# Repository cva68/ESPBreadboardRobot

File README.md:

# ESP32 Breadboard Robot
A device designed to mount to a breadboard to breakout the ESP32-C3 devboard pins, add an LED matrix, dual motor drivers, photoresistor inputs for line following, and two buttons.
Designed to mimic (some) functionality of the BBC micro:bit + Kitronic Motor Driver Board combo currently used by Lincoln High School for teaching electronics, at a lower cost and in a more convenient package.

## Software
The software is designed to support exporting blocks from MakeCode directly into main.py. Basic, LED, Input and Motor blocks are currently supported. src/ and lib/ have the required files to enable this.

## Hardware
The schematic and PCB designs are included in /hardware.

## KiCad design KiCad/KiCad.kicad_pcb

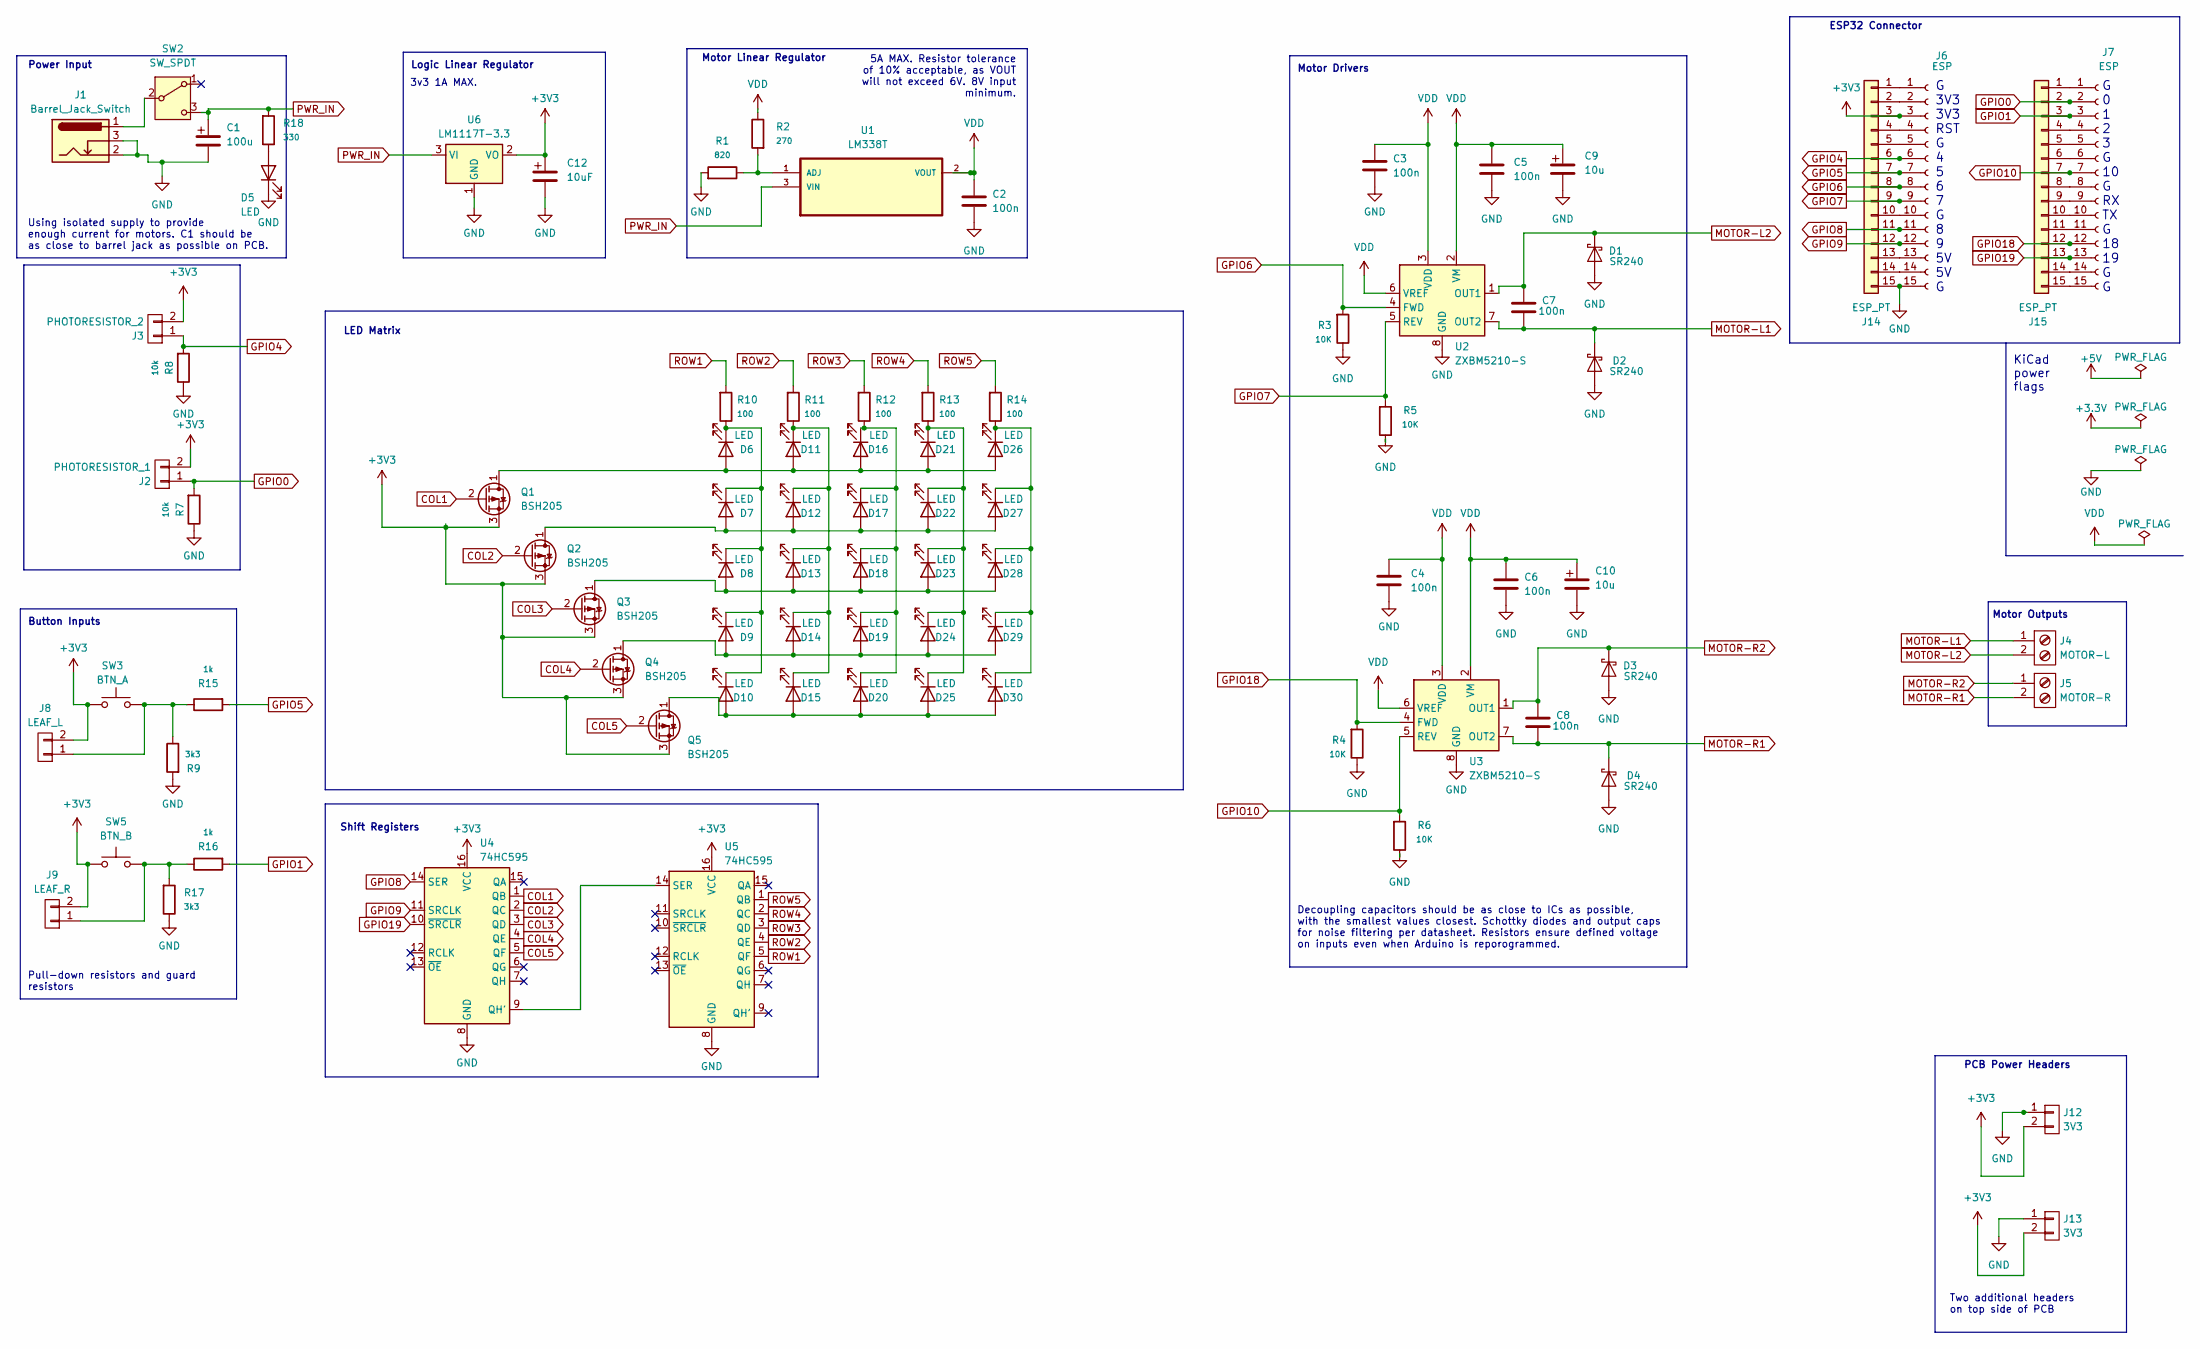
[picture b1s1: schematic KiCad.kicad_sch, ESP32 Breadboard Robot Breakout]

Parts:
C1: 100u; CP_Radial_D8.0mm_P3.50mm
C2, C3, C4, C5, C6, C7, C8: 100n; C_Rect_L4.6mm_W3.0mm_P2.50mm_MKS02_FKP02
C9, C10: 10u; CP_Radial_D8.0mm_P3.50mm
C12: 10uF; CP_Radial_D5.0mm_P2.00mm
D1, D2, D3, D4: SR240; D_DO-35_SOD27_P2.54mm_Vertical_AnodeUp
D5: LED; LED_D5.0mm
D6, D7, D8, D9, D10, D11, D12, D13, D14, D15, D16, D17, D18, D19, D20, D21, D22, D23, D24, D25, D26, D27, D28, D29, D30: LED; LED_1206_3216Metric_Pad1.42x1.75mm_HandSolder
J1: Barrel_Jack_Switch; BarrelJack_Horizontal
J2: PHOTORESISTOR_1; PinHeader_1x02_P2.54mm_Vertical
J3: PHOTORESISTOR_2; PinHeader_1x02_P2.54mm_Vertical
J4: MOTOR-L; TerminalBlock_Phoenix_MKDS-1,5-2-5.08_1x02_P5.08mm_Horizont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
J5: MOTOR-R; TerminalBlock_Phoenix_MKDS-1,5-2-5.08_1x02_P5.08mm_Horizont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
J6, J7: ESP; PinHeader_1x15_P2.54mm_Vertical
J8: LEAF_L; PinHeader_1x02_P2.54mm_Vertical
J9: LEAF_R; PinHeader_1x02_P2.54mm_Vertical
J12, J13: 3V3; PinHeader_1x02_P2.54mm_Vertical
J14, J15: ESP_PT; PinHeader_1x15_P2.54mm_Vertical
Q1, Q2, Q3, Q4, Q5: BSH205; SOT-23-3
R1: 820; R_Axial_DIN0207_L6.3mm_D2.5mm_P2.54mm_Vertical
R2: 270; R_Axial_DIN0207_L6.3mm_D2.5mm_P2.54mm_Vertical
R3, R4, R5, R6: 10K; R_Axial_DIN0207_L6.3mm_D2.5mm_P2.54mm_Vertical
R7, R8: 10k; R_Axial_DIN0207_L6.3mm_D2.5mm_P2.54mm_Vertical
R9, R17: 3k3; R_Axial_DIN0207_L6.3mm_D2.5mm_P2.54mm_Vertical
R10, R11, R12, R13, R14: 100; R_Axial_DIN0207_L6.3mm_D2.5mm_P2.54mm_Vertical
R15, R16: 1k; R_Axial_DIN0207_L6.3mm_D2.5mm_P2.54mm_Vertical
R18: 330; R_Axial_DIN0207_L6.3mm_D2.5mm_P2.54mm_Vertical
SW2: SW_SPDT; SW_Slide-03_Wuerth-WS-SLTV_10x2.5x6.4_P2.54mm
SW3: BTN_A; SW_PUSH_6mm_H5mm
SW5: BTN_B; SW_PUSH_6mm_H5mm
U1: LM338T; TO-220-3_Horizontal_TabDown
U2, U3: ZXBM5210-S; SOIC-8_3.9x4.9mm_P1.27mm
U4, U5: 74HC595; SOIC-16_4.55x10.3mm_P1.27mm
U6: LM1117T-3.3; TO-220-3_Horizontal_TabDown

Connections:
+3V3: C12.1, J2.2, J3.2, J6.3, J8.2, J9.2, J12.2, J13.2, J14.3, Q1.3 (S), Q2.3 (S), Q3.3 (S), Q4.3 (S), Q5.3 (S), SW3.1, SW5.1, U4.16 (VCC), U5.16 (VCC), U6.2 (VO)
COL1: Q1.2 (G), U4.1 (QB)
COL2: Q2.2 (G), U4.2 (QC)
COL3: Q3.2 (G), U4.3 (QD)
COL4: Q4.2 (G), U4.4 (QE)
COL5: Q5.2 (G), U4.5 (QF)
GND: C1.2, C2.2, C3.2, C4.2, C5.2, C6.2, C9.2, C10.2, C12.2, D1.2 (A), D2.2 (A), D3.2 (A), D4.2 (A), D5.1 (K), J1.2, J1.3, J6.15, J12.1, J13.1, J14.15, R1.1, R3.2, R4.2, R5.2, R6.2, R7.2, R8.2, R9.1, R17.2, U2.8 (GND), U3.8 (GND), U4.8 (GND), U5.8 (GND), U6.1 (GND)
GPIO0: J2.1, J7.2, J15.2, R7.1
GPIO1: J7.3, J15.3, R16.1
GPIO4: J3.1, J6.6, J14.6, R8.1
GPIO5: J6.7, J14.7, R15.1
GPIO6: J6.8, J14.8, R3.1, U2.4 (FWD)
GPIO7: J6.9, J14.9, R5.1, U2.5 (REV)
GPIO8: J6.11, J14.11, U4.14 (SER)
GPIO9: J6.12, J14.12, U4.11 (SRCLK)
GPIO10: J7.7, J15.7, R6.1, U3.5 (REV)
GPIO18: J7.12, J15.12, R4.1, U3.4 (FWD)
GPIO19: J7.13, J15.13, U4.10 (~SRCLR)
MOTOR-L1: C7.2, D2.1 (K), J4.1, U2.7 (OUT2)
MOTOR-L2: C7.1, D1.1 (K), J4.2, U2.1 (OUT1)
MOTOR-R1: C8.2, D4.1 (K), J5.2, U3.7 (OUT2)
MOTOR-R2: C8.1, D3.1 (K), J5.1, U3.1 (OUT1)
unnamed: D5.2 (A), R18.2
unnamed: D10.2 (A), D15.2 (A), D20.2 (A), D25.2 (A), D30.2 (A), Q5.1 (D)
unnamed: D6.1 (K), D7.1 (K), D8.1 (K), D9.1 (K), D10.1 (K), R10.2
unnamed: D6.2 (A), D11.2 (A), D16.2 (A), D21.2 (A), D26.2 (A), Q1.1 (D)
unnamed: D11.1 (K), D12.1 (K), D13.1 (K), D14.1 (K), D15.1 (K), R11.2
unnamed: D7.2 (A), D12.2 (A), D17.2 (A), D22.2 (A), D27.2 (A), Q2.1 (D)
unnamed: D8.2 (A), D13.2 (A), D18.2 (A), D23.2 (A), D28.2 (A), Q3.1 (D)
unnamed: D9.2 (A), D14.2 (A), D19.2 (A), D24.2 (A), D29.2 (A), Q4.1 (D)
unnamed: D16.1 (K), D17.1 (K), D18.1 (K), D19.1 (K), D20.1 (K), R12.2
unnamed: D21.1 (K), D22.1 (K), D23.1 (K), D24.1 (K), D25.1 (K), R13.2
unnamed: D26.1 (K), D27.1 (K), D28.1 (K), D29.1 (K), D30.1 (K), R14.2
unnamed: J8.1, R9.2, R15.2, SW3.2
unnamed: J9.1, R16.2, R17.1, SW5.2
unnamed: J6.1, J14.1
unnamed: J6.2, J14.2
unnamed: J6.4, J14.4
unnamed: J6.5, J14.5
unnamed: J6.10, J14.10
unnamed: J6.13, J14.13
unnamed: J6.14, J14.14
unnamed: J7.1, J15.1
unnamed: J7.4, J15.4
unnamed: J7.5, J15.5
unnamed: J7.6, J15.6
unnamed: J7.8, J15.8
unnamed: J7.9, J15.9
unnamed: J7.10, J15.10
unnamed: J7.11, J15.11
unnamed: J7.14, J15.14
unnamed: J7.15, J15.15
unnamed: J1.1, SW2.2 (B)
unnamed: R1.2, R2.1, U1.1 (ADJ)
unnamed: U4.9 (QH'), U5.14 (SER)
PWR_IN: C1.1, R18.1, SW2.3 (C), U1.3 (VIN), U6.3 (VI)
ROW1: R10.1, U5.5 (QF)
ROW2: R11.1, U5.4 (QE)
ROW3: R12.1, U5.3 (QD)
ROW4: R13.1, U5.2 (QC)
ROW5: R14.1, U5.1 (QB)
VDD: C2.1, C3.1, C4.1, C5.1, C6.1, C9.1, C10.1, R2.2, U1.2 (VOUT), U2.2 (VM), U2.3 (VDD), U2.6 (VREF), U3.2 (VM), U3.3 (VDD), U3.6 (VREF)

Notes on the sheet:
5A MAX. Resistor tolerance of 10% acceptable, as VOUT will not exceed 6V. 8V input minimum.
Motor Outputs
Motor Linear Regulator
G 3V3 3V3 RST G 4 5 6 7 G 8 9 5V 5V G
Button Inputs
Two additional headers on top side of PCB
3v3 1A MAX.
LED Matrix
KiCad power flags
Motor Drivers
Logic Linear Regulator
G 0 1 2 3 G 10 G RX TX G 18 19 G G
Pull-down resistors and guard resistors
Shift Registers
Decoupling capacitors should be as close to ICs as possible, with the smallest values closest. Schottky diodes and output caps for noise filtering per datasheet. Resistors ensure defined voltage on inputs even when Arduino is reporogrammed.
PCB Power Headers
ESP32 Connector
Using isolated supply to provide enough current for motors. C1 should be as close to barrel jack as possible on PCB.
Power Input

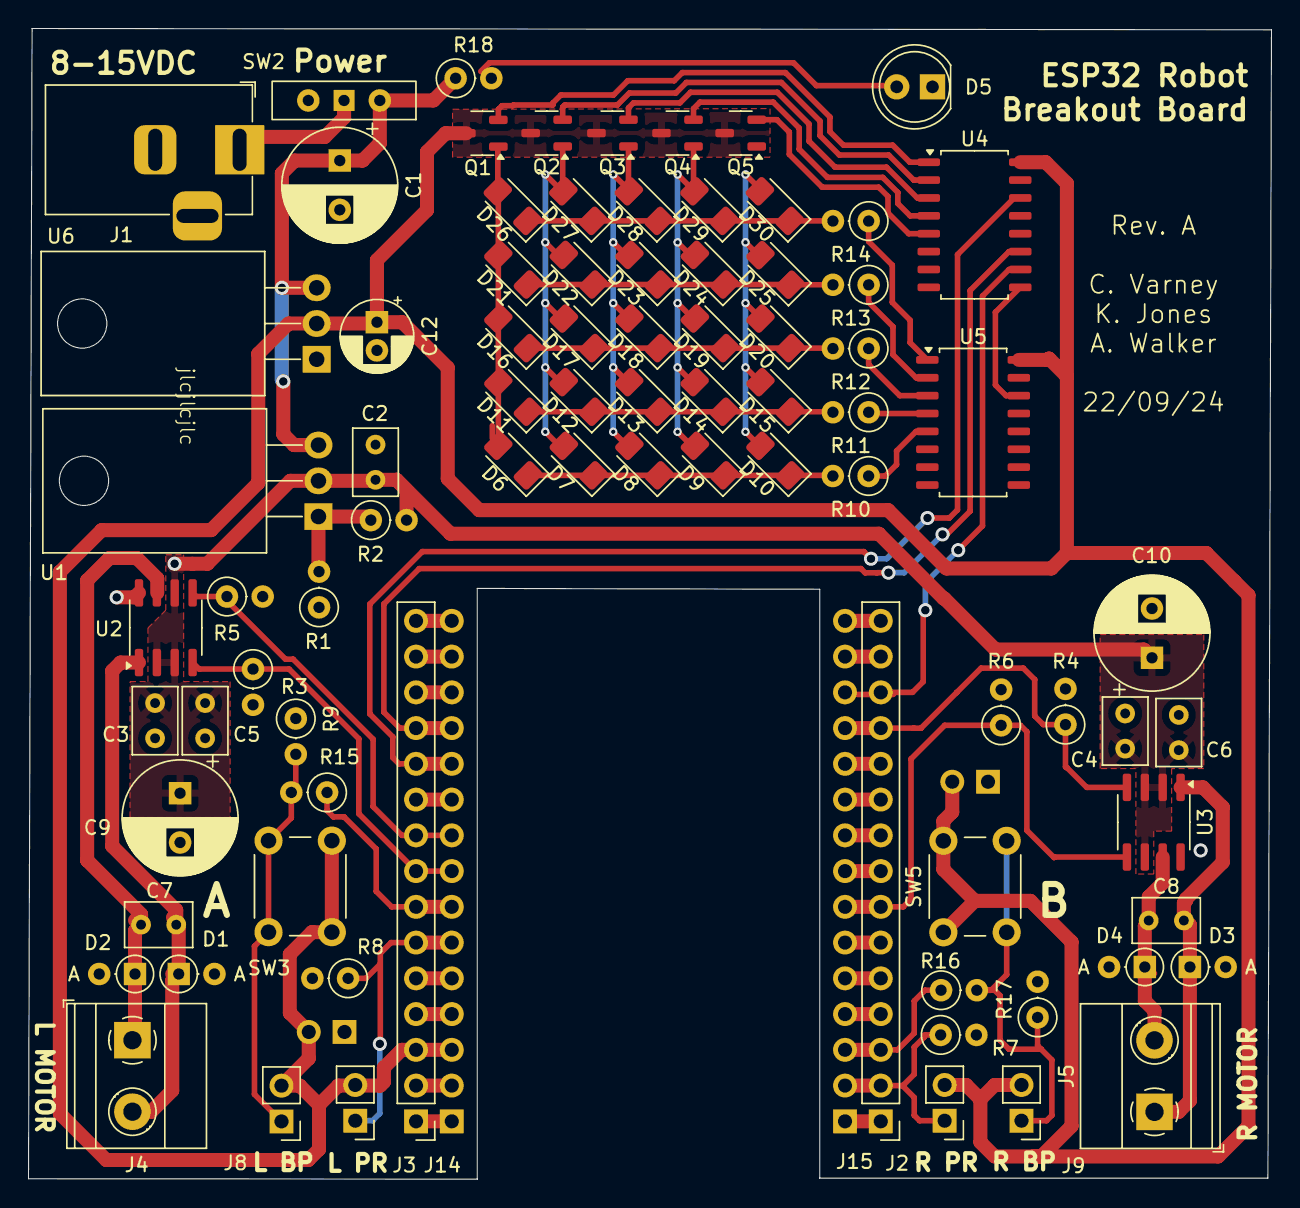
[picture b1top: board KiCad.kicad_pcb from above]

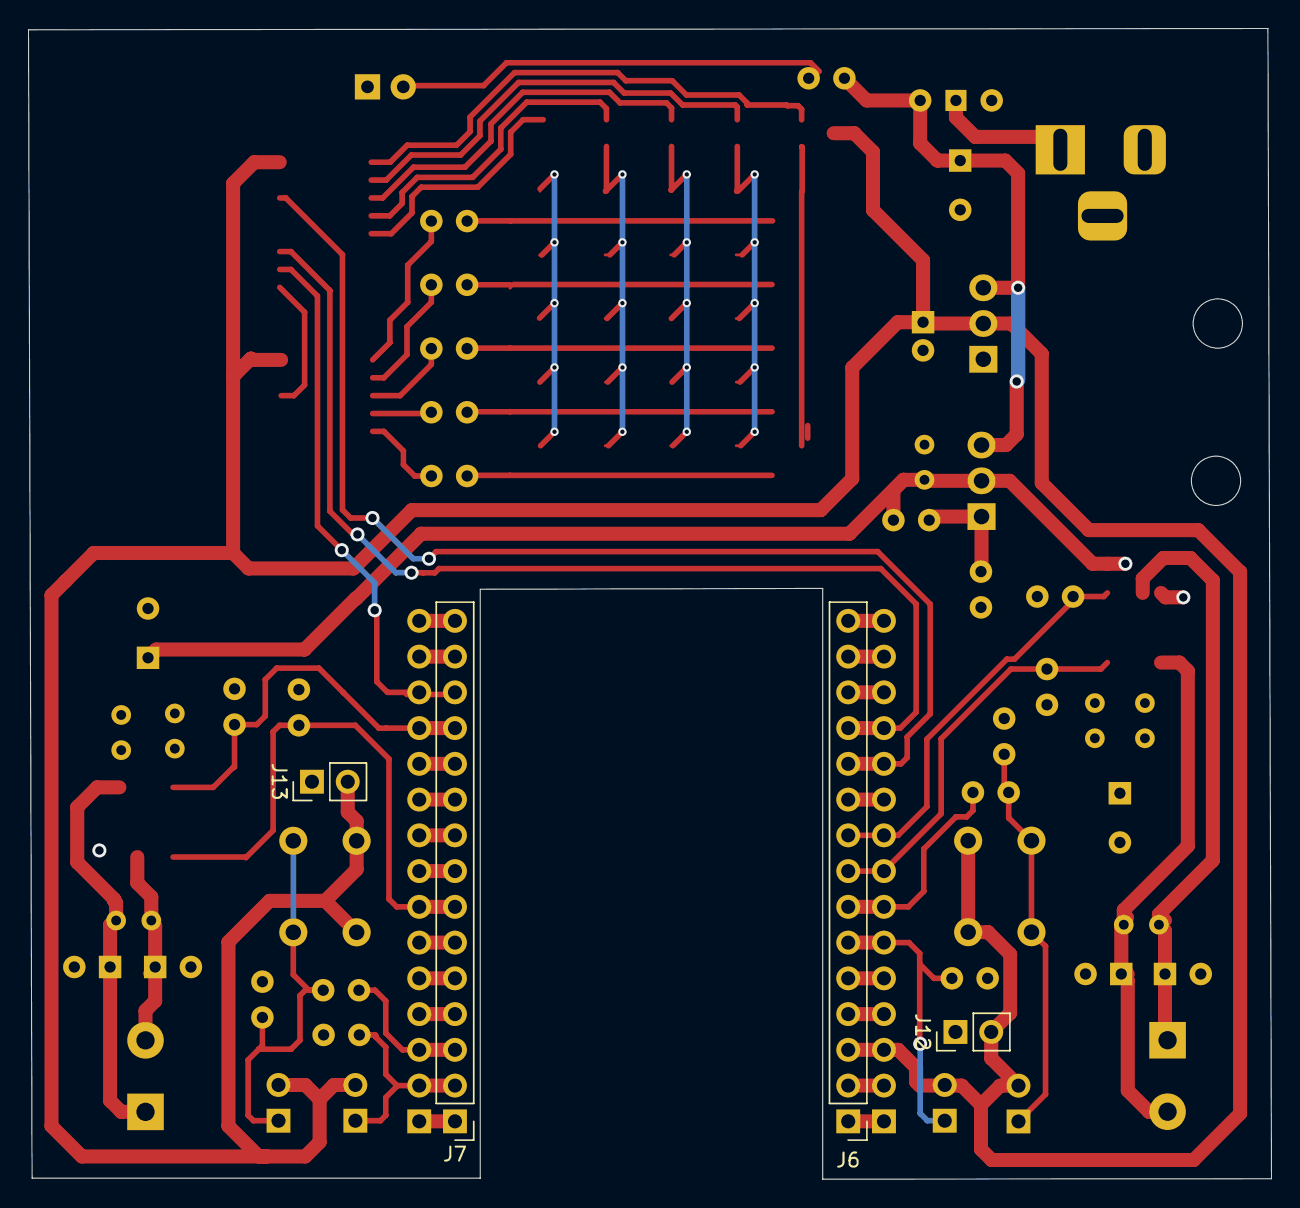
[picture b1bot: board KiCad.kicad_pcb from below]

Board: 2 copper layers, 88.3 x 81.8 mm, 86 parts (4 on the bottom side), 62 nets.

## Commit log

2024-09-19 Initial PCB design
2024-09-19 Added shift registers, finished LED matrix
2024-09-21 Finished Rev A schematic
2024-09-21 Added NC markers, title and date
2024-09-22 PCB Revision A Created
2024-09-22 fixed kahus clever commit
2024-09-22 fixed connors clever commit
2024-09-24 final pcb rev
2024-09-30 basic class setup
2024-09-30 adding classes and function placeholders
2024-10-01 restructured, added schema and pcb layout
2024-10-01 Restructured directories
2024-10-05 Restructured, added LED test script
2024-10-06 added input class and motor driver class
2024-10-06 Initial testing of the LED matrix software
2024-10-06 Updated LED code
2024-10-06 clearing main
2024-10-06 all classes get setup outside of main
2024-10-06 threading update display function
2024-10-06 Fixed missing self reference
2024-10-06 some basic functions and a tidy
2024-10-07 changed led to send tuples
2024-10-07 More LED testing
2024-10-07 merge?
2024-10-07 led plot
2024-10-07 LED Testing
2024-10-07 plot, unplot, toggle functions added to led
2024-10-07 fixed incoming change
2024-10-08 Removed modules not implemented
2024-10-08 Fixed LED plotting from MakeCode pattern, removed functions not implemented
2024-10-18 Final software revisions
2024-10-18 Added License
